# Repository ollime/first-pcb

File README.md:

A PCB that has a button to light up two LEDs and another button that vibrates a motor.

Features some of my favorite emojis at https://fonts.google.com/noto/specimen/Noto+Emoji

## Schematic

## PCB

## 3D Model

## BOM

- 1 BatteryHolder_Keystone_3034_1x20mm
- 2 LED_D5.0mm
- 2 R_Axial_DIN0207_L6.3mm_D2.5mm_P7.62mm_Horizontal
- 2 SW_PUSH_6mm
- 1 PinHeader_1x02_P2.54mm_Vertical

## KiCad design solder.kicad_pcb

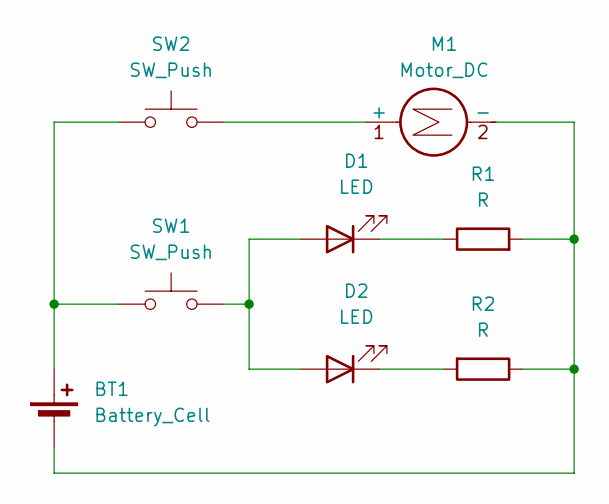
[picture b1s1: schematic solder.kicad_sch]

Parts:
BT1: Battery_Cell; BatteryHolder_Keystone_3034_1x20mm
D1, D2: LED; LED_D5.0mm
M1: Motor_DC; PinHeader_1x02_P2.54mm_Vertical
R1, R2: R; R_Axial_DIN0207_L6.3mm_D2.5mm_P7.62mm_Horizontal
SW1, SW2: SW_Push; SW_PUSH_6mm

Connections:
unnamed: BT1.1 (+), SW1.1, SW2.1
unnamed: BT1.2 (-), M1.2 (-), R1.2, R2.1
unnamed: D1.2 (A), D2.2 (A), SW1.2
unnamed: D1.1 (K), R1.1
unnamed: D2.1 (K), R2.2
unnamed: M1.1 (+), SW2.2

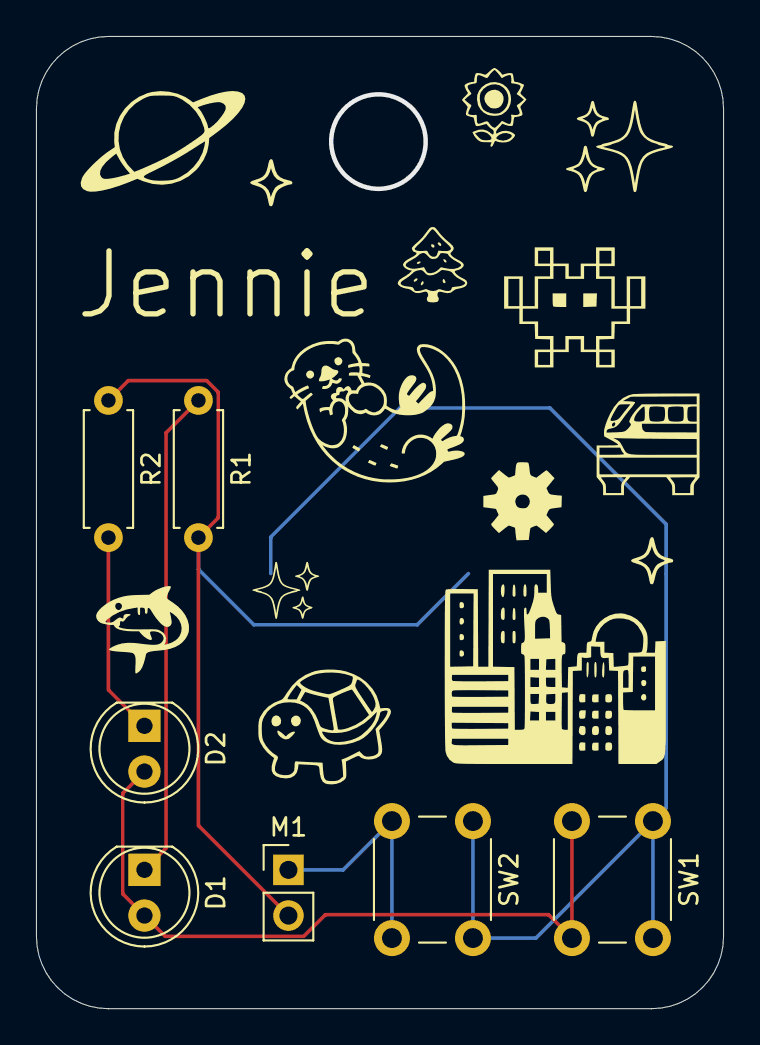
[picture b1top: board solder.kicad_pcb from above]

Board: 2 copper layers, 38.2 x 54.0 mm, 8 parts (1 on the bottom side), 6 nets.

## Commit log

2025-05-31 added README
2025-05-31 added routing
2025-05-31 rotated motor
2025-05-31 added keychain hole back
2025-05-31 fixed routing
2025-05-31 gitignore
2025-06-02 added to back silkscreen, rotated the pcb, added name
2025-06-02 added gerbers.zip
